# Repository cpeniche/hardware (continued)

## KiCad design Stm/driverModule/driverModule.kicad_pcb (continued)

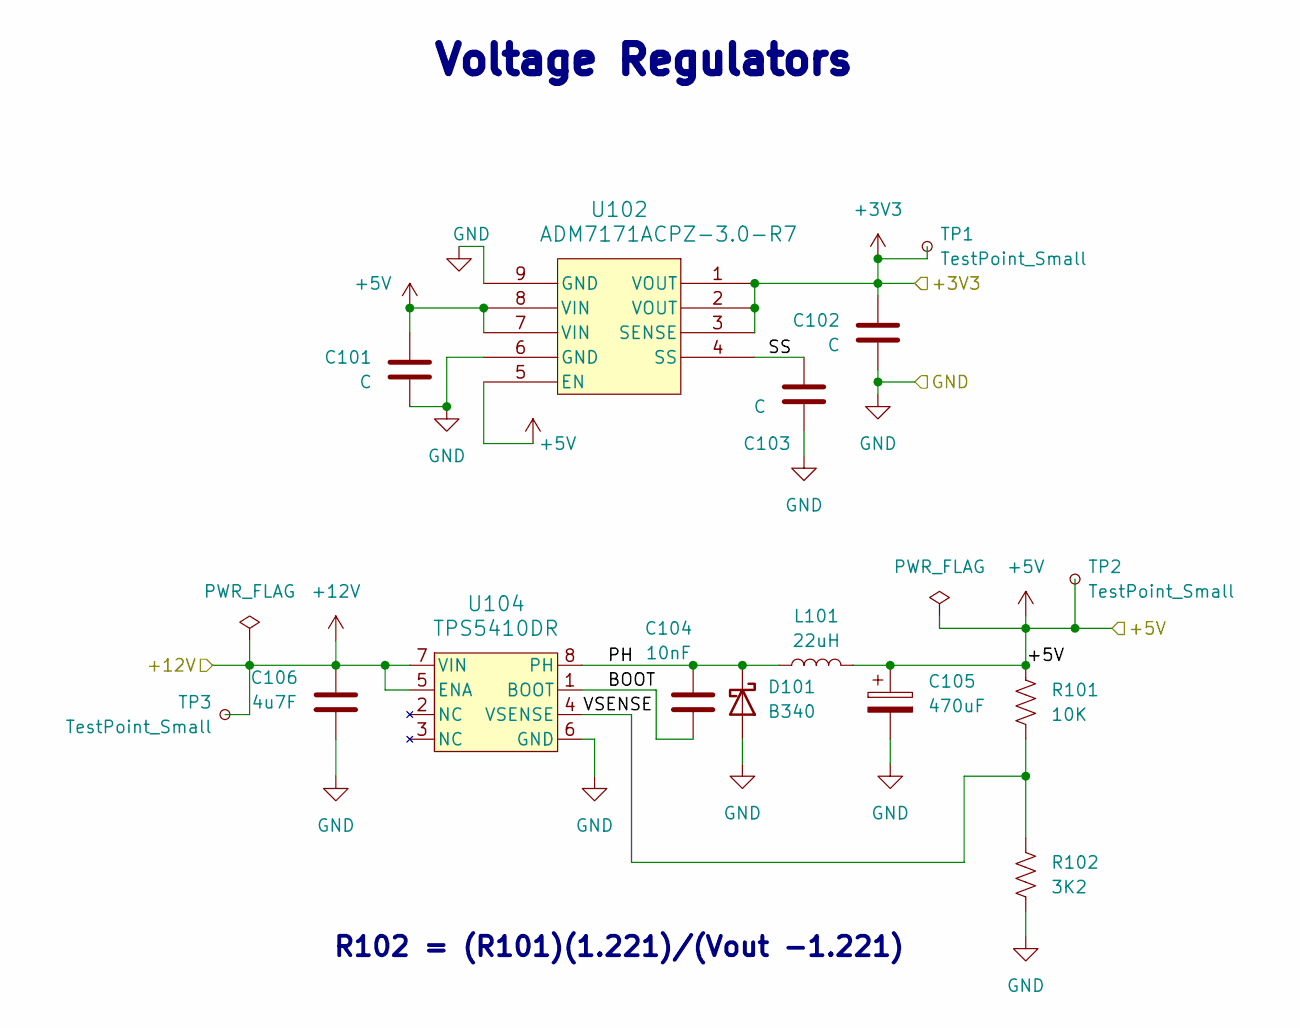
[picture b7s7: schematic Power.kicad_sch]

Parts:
C101, C102, C103: C; C_0402_1005Metric_Pad0.74x0.62mm_HandSolder
C104: 10nF; C_0805_2012Metric
C105: 470uF; CP_EIA-7132-20_AVX-U
C106: 4u7F; C_0805_2012Metric
D101: B340; D_SMC
L101: 22uH; L-SMD-13.45x12.6X5.0mm
R101: 10K; R_0402_1005Metric_Pad0.72x0.64mm_HandSolder
R102: 3K2; R_0402_1005Metric_Pad0.72x0.64mm_HandSolder
TP1, TP2, TP3: TestPoint_Small; TestPoint_Pad_1.0x1.0mm
U102: ADM7171ACPZ-3.0-R7; LFCSP-8-1EP_3x3mm_P0.5mm_EP_1.70x2.54mm
U104: TPS5410DR; SOIC-8-1EP_3.9x4.9mm_P1.27mm

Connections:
+3V3: C102.1, TP1.1, U102.1 (VOUT), U102.2 (VOUT), U102.3 (SENSE); also elsewhere on the board
+5V: C101.1, C105.1, L101.2, R101.1, TP2.1, U102.5 (EN), U102.7 (VIN), U102.8 (VIN); also elsewhere on the board
+12V: C106.2, TP3.1, U104.5 (ENA), U104.7 (VIN); also elsewhere on the board
/Power/BOOT: C104.1, U104.1 (BOOT)
/Power/PH: C104.2, D101.1 (K), L101.1, U104.8 (PH)
/Power/SS: C103.1, U102.4 (SS)
/Power/VSENSE: R101.2, R102.1, U104.4 (VSENSE)
GND: C101.2, C102.2, C103.2, C105.2, C106.1, D101.2 (A), R102.2, U102.6 (GND), U102.9 (GND), U104.6 (GND); also elsewhere on the board

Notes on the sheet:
R102 = (R101)(1.221)/(Vout -1.221)
Voltage Regulators

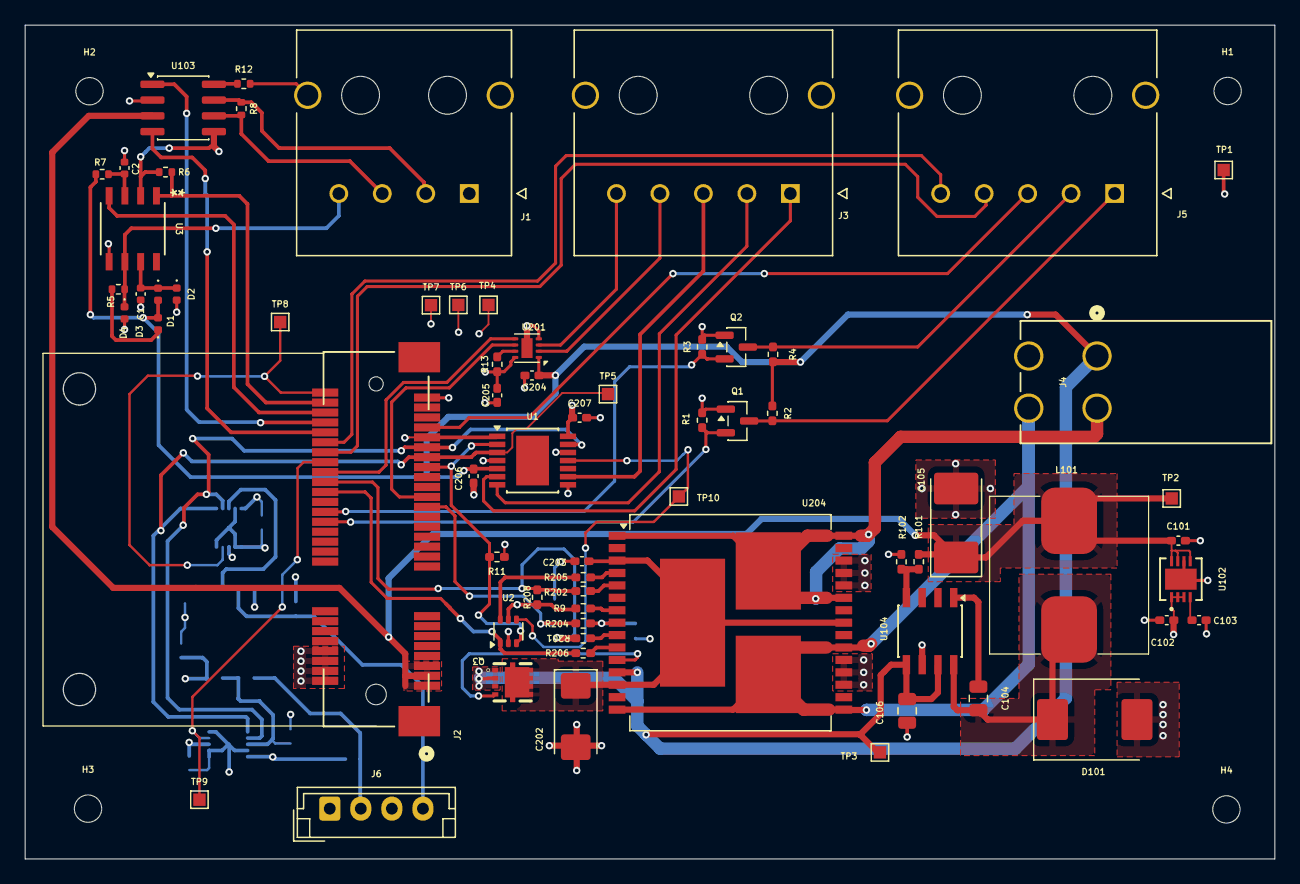
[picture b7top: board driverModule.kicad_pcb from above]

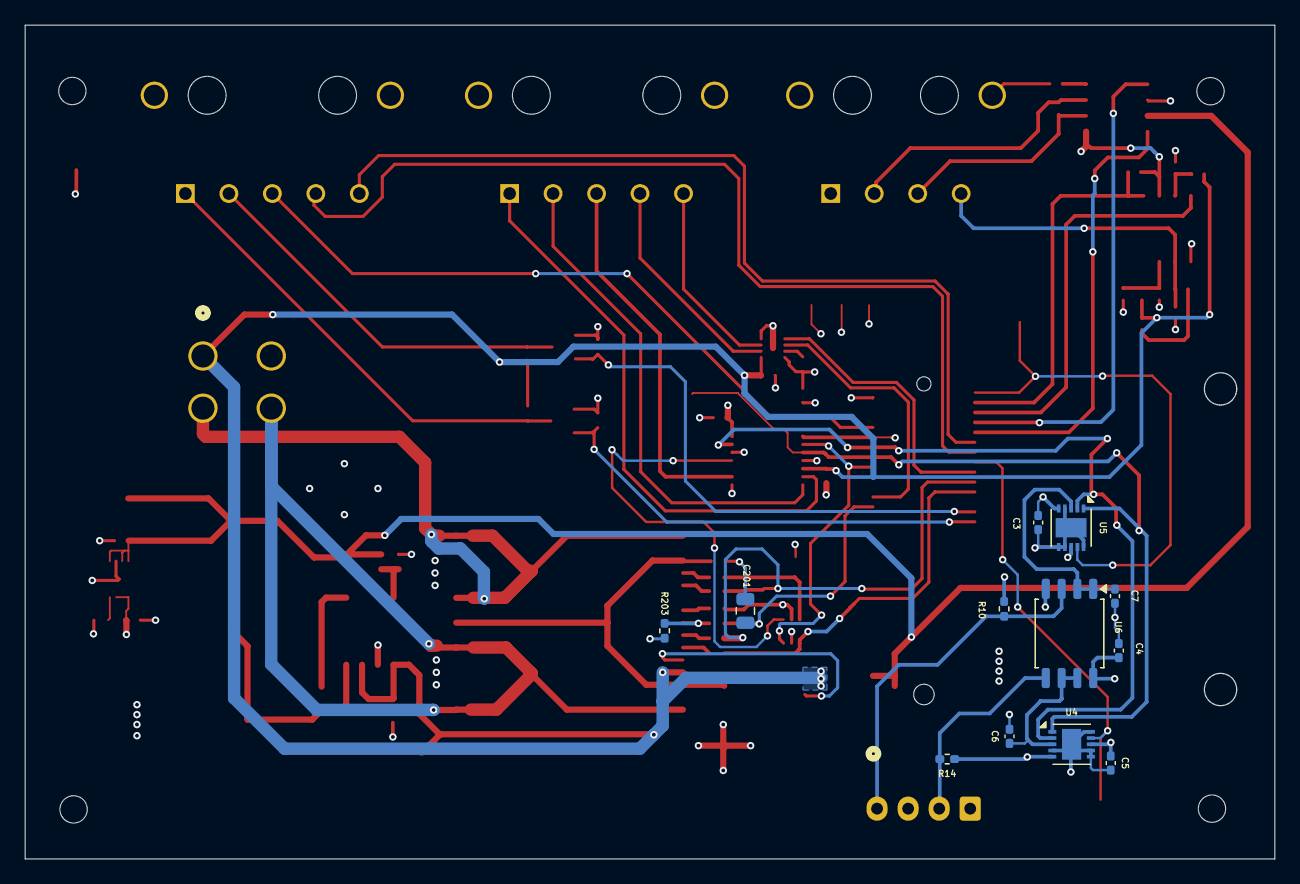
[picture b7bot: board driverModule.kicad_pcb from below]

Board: 4 copper layers, 100.6 x 67.1 mm, 83 parts (12 on the bottom side), 59 nets.

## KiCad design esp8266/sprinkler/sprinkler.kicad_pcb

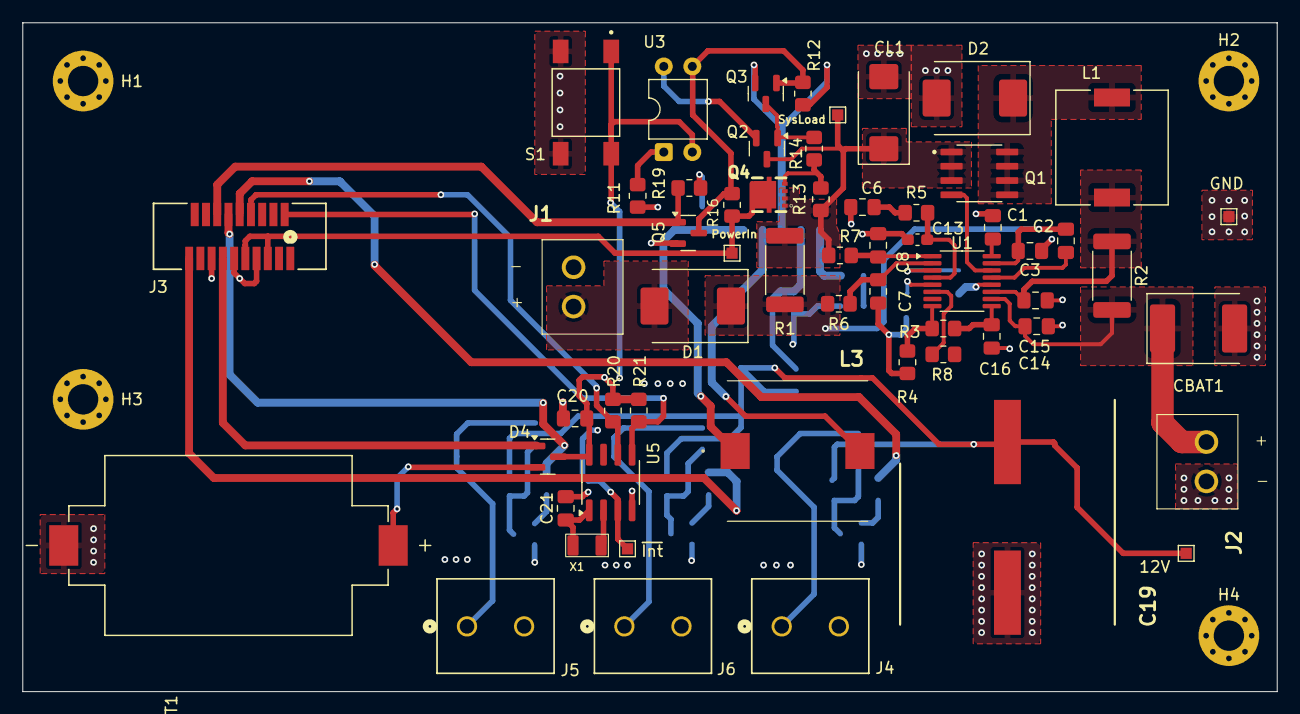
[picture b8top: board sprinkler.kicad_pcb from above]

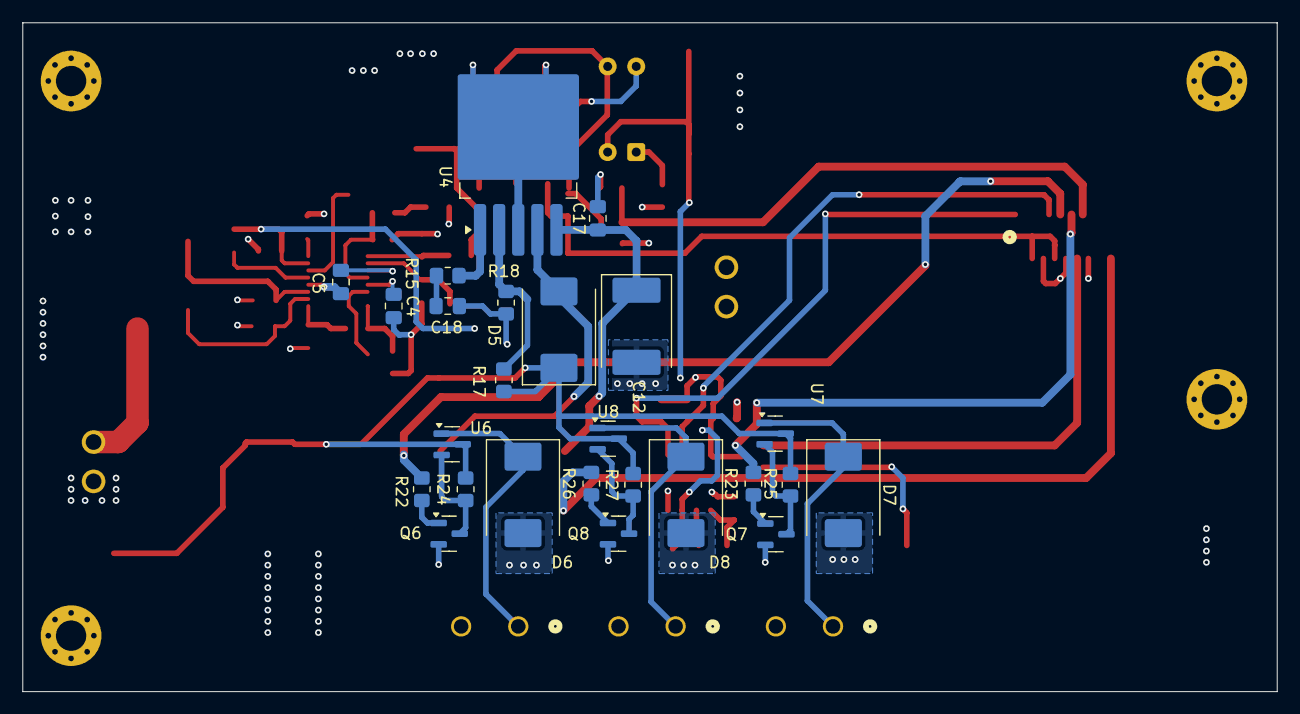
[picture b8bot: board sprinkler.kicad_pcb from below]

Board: 4 copper layers, 111.6 x 59.5 mm, 86 parts (25 on the bottom side), 52 nets.

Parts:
12V: TestPoint; TestPoint_Pad_1.0x1.0mm
BT1: CR-2032_1060; BAT_1060
C1: 2u2nF; C_0805_2012Metric_Pad1.18x1.45mm_HandSolder
C2, C3: 220nF; C_0805_2012Metric_Pad1.18x1.45mm_HandSolder
C4, C5: 47nF; C_0805_2012Metric_Pad1.18x1.45mm_HandSolder
C6: 100nf; C_0805_2012Metric_Pad1.18x1.45mm_HandSolder
C7, C8: 100nF; C_0805_2012Metric_Pad1.18x1.45mm_HandSolder
C12: 220uF; CP_EIA-7360-38_Kemet-E_HandSolder
C13: 1nF; C_0603_1608Metric_Pad1.08x0.95mm_HandSolder
C14, C15, C17, C20: 0u1F; C_0805_2012Metric_Pad1.18x1.45mm_HandSolder
C16: 1uF; C_0805_2012Metric_Pad1.18x1.45mm_HandSolder
C18: 820nF; C_0805_2012Metric_Pad1.18x1.45mm_HandSolder
C19: 1000uF; CAPAE1910X2250N
C21: 100pF; C_0805_2012Metric_Pad1.18x1.45mm_HandSolder
CBAT1: 68uF; CP_EIA-7360-38_Kemet-E_HandSolder
CL1: 47uF; CP_EIA-7343-31_Kemet-D_HandSolder
D1, D2, D5: MBRS340; D_SMC
D4: BAT54C; SOT-23
D6, D7, D8: B340; D_SMC
GND: TestPoint; TestPoint_Pad_1.0x1.0mm
H1, H2, H3, H4: MountingHole_Pad_MP; MountingHole_2.7mm_Pad_Via
J1, J2: Terminal Block 1729128; OQ0212500000G
J3: DF9B-19P-1V32; CON9_1X19_MDL_DF9_HIR
J4, J5, J6: Terminal Block 1729128; CONN_1729128_PXC
L1: CDRH105RNP-100NC; IND_CDRH105RNP-100NC
L3: 220uH; SLF12575
PowerIn: TestPoint; TestPoint_Pad_1.0x1.0mm
Q1: AO4407A; SOIC127P600X175-8N
Q2, Q3, Q5: 2N7002; SOT-23
Q4: AON7401; DFN_3X3_EP
Q6, Q7, Q8: MMBT2222A; SOT-23
R1: 33m; R_2512_6332Metric_Pad1.40x3.35mm_HandSolder
R2: 68m; R_2512_6332Metric_Pad1.40x3.35mm_HandSolder
R3, R4, R8, R13, R14: 100K; R_0805_2012Metric_Pad1.20x1.40mm_HandSolder
R5, R12, R20, R21: 10K; R_0805_2012Metric_Pad1.20x1.40mm_HandSolder
R6, R7: 4.7; R_0805_2012Metric_Pad1.20x1.40mm_HandSolder
R11: 100; R_0805_2012Metric_Pad1.20x1.40mm_HandSolder
R15: 1K5; R_0805_2012Metric_Pad1.20x1.40mm_HandSolder
R16: 50K; R_0805_2012Metric_Pad1.20x1.40mm_HandSolder
R17: 17K4; R_0805_2012Metric_Pad1.20x1.40mm_HandSolder
R18: 2K; R_0805_2012Metric_Pad1.20x1.40mm_HandSolder
R19: 1M; R_0805_2012Metric_Pad1.20x1.40mm_HandSolder
R22, R23, R24, R25, R26, R27: 15K; R_0805_2012Metric_Pad1.20x1.40mm_HandSolder
S1: TS04-66-70-BK-260-SMT; SW_TS04-66-70-BK-260-SMT
SysLoad: TestPoint; TestPoint_Pad_1.0x1.0mm
U1: MAX1873TEEE; QSOP-16_3.9x4.9mm_P0.635mm
U3: PC817; DIP-4_W7.62mm
U4: LM2577S-ADJ_NOPB; TO-263-5_TabPin3
U5: PCF8563T; SOIC-8_3.9x4.9mm_P1.27mm
U6, U7, U8: MMBT2907A-7-F; SOT-23
X1: DST310S

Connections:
+12V: 12V.1, C19.1 (+), D5.1 (K), R17.1, R24.1, R25.1, R27.1, U6.3 (E), U7.3 (E), U8.3 (E)
/Microcontroller/IO12: J3.10, R22.1
/Microcontroller/IO13: J3.12, R23.1
/Microcontroller/IO14: J3.19, R26.1
/Microcontroller/PowerIn: J3.5, J3.9, PowerIn.1, Q4.5 (D), Q4.6 (D), Q4.7 (D), Q4.8 (D), R16.1
/Microcontroller/SCL: J3.8, R20.2, U5.6 (SCL)
/Microcontroller/SDA: J3.2, R21.2, U5.5 (SDA)
/Microcontroller/SwitchOff: J3.14, Q5.1 (G), R19.1
/Microcontroller/esp8266_3V3: D4.1, J3.13
/Power Sheet/3V3: C20.1, D4.3, R11.1, R20.1, R21.1, U5.8 (VDD)
/Power Sheet/Power_In: C12.1, C17.1, L3.1, U4.5 (VIN)
/Power Sheet/SolarPower: D1.2 (A), J1.2
/Power Sheet/SysLoad: CL1.1, Q1.1, Q1.2, Q1.3, Q2.3 (D), Q4.1 (S), Q4.2 (S), Q4.3 (S), R1.1, R7.2, R13.1, SysLoad.1
/Power Sheet/~Int: S1.1, S1.3, U3.2, U5.3 (~INT)
GND: BT1.N, C1.1, C3.1, C4.2, C5.2, C6.2, C7.1, C8.1, C12.2, C13.2, C14.1, C15.1, C16.1, C17.2, C18.2, C19.2 (-), C20.2, C21.2, CBAT1.2, CL1.2, D2.2 (A), D6.2 (A), D7.2 (A), D8.2 (A), GND.1, J1.1, J2.1, J3.7, J3.11, J3.15, J4.2, J5.2, J6.2, Q3.2 (S), Q5.2 (S), Q6.2 (E), Q7.2 (E), Q8.2 (E), R4.2, R12.2, R18.2, R19.2, S1.2, S1.4, U1.12 (GND), U4.3 (GROUND), U5.4 (VSS)
unnamed: BT1.P, D4.2
unnamed: C6.1, R5.2
unnamed: C18.1, R15.2
unnamed: C2.2, C3.2, D1.1 (K), R1.2, R6.2, U1.15 (DCIN)
unnamed: D2.1 (K), L1.1, Q1.5, Q1.6, Q1.7, Q1.8
unnamed: D5.2 (A), L3.2, U4.4 (SWITCH)
unnamed: D6.1 (K), J4.1, U6.1 (C)
unnamed: D7.1 (K), J5.1, U7.1 (C)
unnamed: D8.1 (K), J6.1, U8.1 (C)
unnamed: Q2.1 (G), Q3.3 (D), R14.2
unnamed: Q2.2 (S), U3.4
unnamed: Q3.1 (G), Q5.3 (D), R12.1, R16.2, U3.3
unnamed: Q4.4 (G), R13.2, R14.1
unnamed: Q6.1 (B), R22.2
unnamed: Q6.3 (C), R24.2, U6.2 (B)
unnamed: Q7.1 (B), R23.2
unnamed: Q7.3 (C), R25.2, U7.2 (B)
unnamed: Q8.1 (B), R26.2
unnamed: Q8.3 (C), R27.2, U8.2 (B)
unnamed: R11.2, U3.1
unnamed: C14.2, CBAT1.1, J2.2, R2.2, U1.10 (BATT)
unnamed: C4.1, U1.5 (CCI)
unnamed: C5.1, U1.3 (CCS)
unnamed: C13.1, R5.1, U1.4 (CCV)
unnamed: C15.2, L1.2, R2.1, U1.11 (CSB)
unnamed: C8.2, R7.1, U1.1 (CSSN)
unnamed: C7.2, R6.1, U1.2 (CSSP)
unnamed: Q1.4, U1.14 (EXT)
unnamed: R8.2, U1.6 (ICHG/EN)
unnamed: C16.2, R3.1, U1.9 (REF)
unnamed: R3.2, R4.1, U1.8 (VADJ)
unnamed: C2.1, U1.13 (VH)
unnamed: C1.2, U1.16 (VL)
unnamed: R15.1, U4.1 (COMP)
unnamed: R17.2, R18.1, U4.2 (FEEDBACK)
unnamed: C21.1, U5.1 (OSCI), X1.1
unnamed: U5.2 (OSCO), X1.2

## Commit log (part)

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2022-03-04 Changed folders
2022-03-04 first revision
    Added 3dparty libraries
2022-03-04 libraries
    Added more libraries
2024-03-13 Add more Project
    Add Arduino hat and Stm32f767 project
2024-03-22 LPC1788_SOM
2024-03-22 Memory connections
2024-03-25 Add sodim connector
2024-03-25 update gitignore
2024-03-25 More connections
2024-06-20 Driver Module Hardware
2024-06-21 Add Headers
2024-06-24 CD40109BNSR
    Added low to high level shifter
    and foot print
2024-06-25 Mirror Motors and key fob
    Changed for a 3 half bridge semiconductor
    Added level shift translator for key fob input
2024-06-25 LPC1788
    Added LPC1788 som module
2024-06-25 Connector
    Removed processor and add a two SMD connectors to plug a MCU carrier board
    Generate first Printed Circuit board layout
2024-06-27 Shift Registers
    Changed shift registers to mc74hc165
2024-06-28 Symbols
    Changed some symbols
    Components placements
2024-06-28 3d Models
    Added Some 3d Models
    And remove some components from schematic
2024-06-28 Esp32-s3
    Initial creation of the carrier module for the esp32-s3
2024-07-01 Carrier Board
    Added Carrier board for the ESP32-XIAO Board
2024-07-01 Routing
    Finish some routing
2024-07-01 Connectors
    Added connector symbols and 3d views
2024-07-01 Connector
    Modify jst connector (Need to look for the correct One)
2024-07-17 Submodule
    Added Sparkfun libraries and footprints
2024-07-31 Remove Connector
2024-08-01 Changed Connector
2024-08-05 PCB Board
    PCB board created, need to verify connectors polarity
2024-08-06 3d Symbols
    Update 3d symbols
2024-09-05 Agilent SPS
2025-07-10 Initial Revision
    Added S3 Wroom-2 carrier board to github
2025-07-10 Unused library formats
    Removed old Kicad symbol libraries
2025-07-10 Rename
    rename user libraries
2025-07-10 Power sheet
    Added Esp32 power sheet and rename previous sheets
2025-07-11 Connectors
    Lower connector routed
2025-07-11 Symbols
    Added New symbols
2025-07-11 Routing
    Routing finished needs to be verify
2025-07-18 database
    Create database library file
2025-07-18 libraries
    Added new libraries
2025-07-18 two layer board
    Final 2 layer board
2025-07-18 libraries
    Add connector DF9B-25S
2025-07-18 Connectors
    change one connector from 21 to 25 pins
    Added test points
2025-07-30 Sprinkler
    Added ESP8266 sprinkler board
2025-07-30 Database
    Add test files for Database implementation
2025-07-30 New Symbols
    added m.2 card symbols and footprint
2025-07-30 New sheets
    Added power sheet and micro controller sheet
2025-07-31 Library
    Added new miscellaneous parts, footprints and 3D viewers.
2025-07-31 Esp8266
    Created a new esp-wroom carrier board
2025-07-31 Sprinklers
    Added RTC and valver drivers modules for the Sprinklers
2025-08-01 Library
    Added New libraries symbols and footprints
2025-08-01 microcontroller
    Wire micro controller pin out to connector
2025-08-04 Board Layout
    Changed board layout to something smaller
2025-08-05 capacitor layout
    Changed capacitor position to front layer to have enough clearance on bottom layer
2025-08-11 Symblols
    added new symbols to library
2025-08-11 Transistor changes
    Changed all Bjt transistors to Mosfets
    Assign footprints
2025-08-12 Labraries
    Added New symbols to Kicad library
2025-08-12 Update connections
    Connect Micro controller inputs and outputs
2025-08-14 symbols
    Add terminal block connector
2025-08-14 Documentation
    Added Documentation folder
2025-08-14 pcb
    First component layout (need to verify ESP8266 board size for fitment)
2025-08-15 Traces
    Layout traces for the PCB
2025-08-18 holes
    Adding mounting holes
2025-11-04 Create stm32g431kb module
2025-11-05 Libraries
    Add Mini PCI Express half card component and update some libraries descriptions
2025-11-05 PCB
    Create pcb
2025-11-06 libraries
    Add description to some libraries
2025-11-06 Pcb
    Add more components
2025-11-07 libraries
    Added new crystal oscillator
2025-11-07 SOM
    Added Card Holes, Needed?
2025-11-08 libraries
    Added usb connector, crystal
2025-11-08 Pcb
    Pre-final PCB
2025-11-10 libraries
    Add mini PCI Express Board connector and add LIN Bus transceiver chip
2025-11-11 Driver Board
    Modify driver module for the PCI express cpu card
2025-11-11 CPU Card
    Specified not connected pins in the schematic
2025-11-11 library
    Changed PCI express connector symbol
2025-11-11 Connector
    Connect all missing inputs and outputs
2025-11-12 Libraries
    Added Molex Mini50 Automotive connector
2025-11-12 Connectors
    Remove some enable signals
    Added Harness connectors
2026-01-01 Update
    Add connection to the harness
2026-01-08 libraries
    Add new molex connectors
2026-01-08 Directories
    Update 3d model directory
2026-01-12 libraries
    Add foot print to libraries
2026-01-12 routing
    Finished PCB routing
2026-01-19 libraries
    Added libraries and 3d models
2026-01-19 Board layout
    Corrected footprints to use 0402
2026-01-19 BOM
    added html bill of materials
2026-01-28 routing
    Update board routing
2026-01-28 Libraries
    Modify some libraries
2026-01-29 library
    Update description
2026-01-29 Pcie Breakout Board
    Create a breakout board for the PCI express card
2026-01-29 PCI Express
    Create breakout board for the PCI express mini card half
2026-01-30 library
    Added ad7171 symbol
2026-01-30 ADC
    Added adc to read passenger input signals
2026-02-03 Capacitors
    Added some filter capacitors
2026-02-06 Small modifications
2026-02-07 Nordic
    added Nordic 52840 board
2026-02-07 Library
    Added NRF52840 symbol
2026-02-07 Update
    Update descriptions
2026-02-07 Fabrication Files
    Added relative directory for fabrication Files
    added fabrication files
2026-02-10 Library
    Added FFC,FPC connector
2026-02-10 pci express Breakoutt Board
    Finished routing
2026-02-13 dirctories
    Add and remove directories
2026-02-19 Libraries
    Add new motor control symbol and inductor
2026-02-19 mpq6524
    Added new breakout board for the MPQ6524 Quad half bridge motor controller
2026-02-20 Paths
    Route some paths
2026-02-20 Motor connector
    Add motor connector
2026-03-03 Connector
    Added Jst Connector 4 position
2026-03-03 Motor connector
    added smd connector for the motor outputs
2026-03-13 footprints
    Update capacitor footprints
2026-03-13 3d models
    Create 3d Models
2026-03-14 traces
    Make traces thicker
2026-03-16 library
    added MP6612G Motor Driver
2026-03-16 MP6612 Board
    Create new board for the MP6612 Motor controller
2026-03-17 libraries
    Add new terminal block and update 3d model connectors
2026-03-17 Layout
    Update layouts for the motor drivers
2026-03-18 library
    added diode footprint
2026-03-18 Rename Project
    Rename project to MP6612
2026-03-20 library
    Added 32 Mhz crystal component
2026-03-20 projects
    Update projects
2026-03-24 library
    added antenna component
2026-03-24 antenna
    Implementing antenna layout
2026-03-24 Design
    adding Nordic semiconductor reference design example
2026-03-24 library
    Added NRF52840 3d model
2026-03-24 layout
    changed Layout
2026-03-25 Update
    Change some footprints and update RF trace
